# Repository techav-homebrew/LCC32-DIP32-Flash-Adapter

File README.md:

# LCC32-DIP32-Flash-Adapter
PCB for using LCC32 29F0x0 flash ROM chips in DIP32 sockets

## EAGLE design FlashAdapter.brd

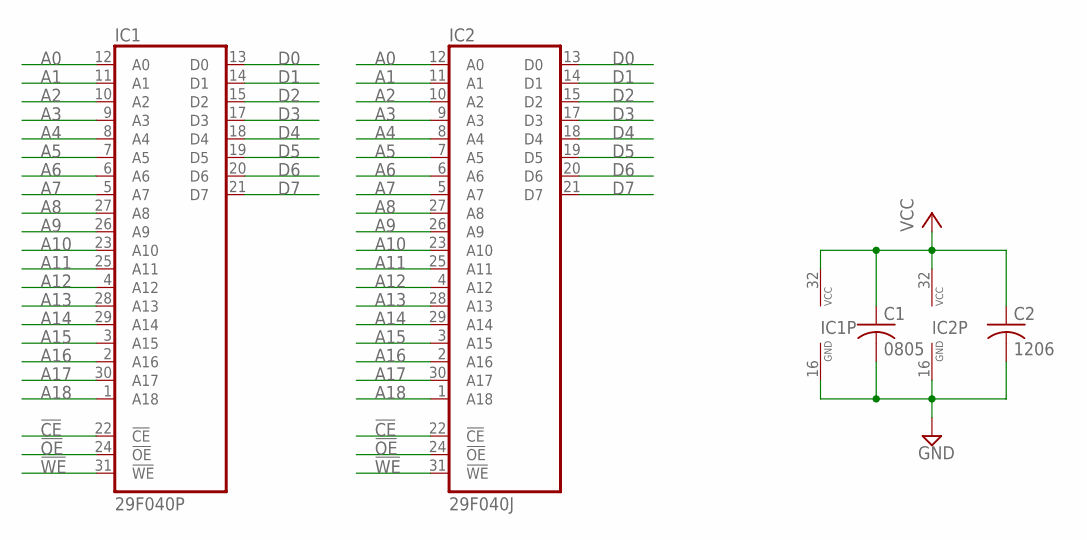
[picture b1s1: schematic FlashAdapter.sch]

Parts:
C1: 0805; C0805
C2: 1206; C1206
IC1: 29F040P; DIL32-3
IC2: 29F040J; S32

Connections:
!CE: IC1.22 (!CE), IC2.22 (!CE)
!OE: IC1.24 (!OE), IC2.24 (!OE)
!WE: IC1.31 (!WE), IC2.31 (!WE)
A0: IC1.12 (A0), IC2.12 (A0)
A1: IC1.11 (A1), IC2.11 (A1)
A2: IC1.10 (A2), IC2.10 (A2)
A3: IC1.9 (A3), IC2.9 (A3)
A4: IC1.8 (A4), IC2.8 (A4)
A5: IC1.7 (A5), IC2.7 (A5)
A6: IC1.6 (A6), IC2.6 (A6)
A7: IC1.5 (A7), IC2.5 (A7)
A8: IC1.27 (A8), IC2.27 (A8)
A9: IC1.26 (A9), IC2.26 (A9)
A10: IC1.23 (A10), IC2.23 (A10)
A11: IC1.25 (A11), IC2.25 (A11)
A12: IC1.4 (A12), IC2.4 (A12)
A13: IC1.28 (A13), IC2.28 (A13)
A14: IC1.29 (A14), IC2.29 (A14)
A15: IC1.3 (A15), IC2.3 (A15)
A16: IC1.2 (A16), IC2.2 (A16)
A17: IC1.30 (A17), IC2.30 (A17)
A18: IC1.1 (A18), IC2.1 (A18)
D0: IC1.13 (D0), IC2.13 (D0)
D1: IC1.14 (D1), IC2.14 (D1)
D2: IC1.15 (D2), IC2.15 (D2)
D3: IC1.17 (D3), IC2.17 (D3)
D4: IC1.18 (D4), IC2.18 (D4)
D5: IC1.19 (D5), IC2.19 (D5)
D6: IC1.20 (D6), IC2.20 (D6)
D7: IC1.21 (D7), IC2.21 (D7)
GND: C1.2, C2.2, IC1.16 (GND), IC2.16 (GND)
VCC: C1.1, C2.1, IC1.32 (VCC), IC2.32 (VCC)

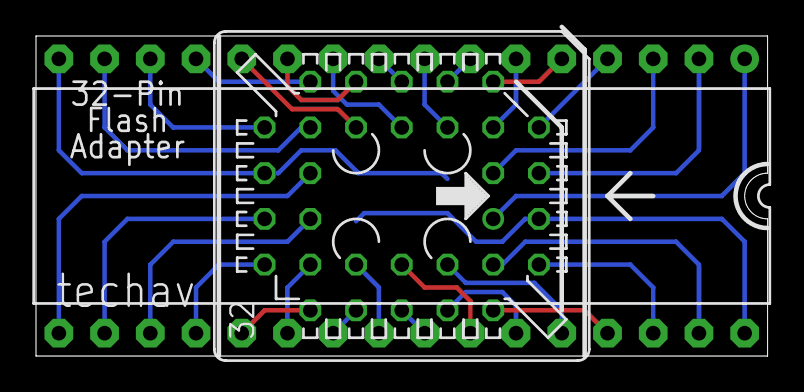
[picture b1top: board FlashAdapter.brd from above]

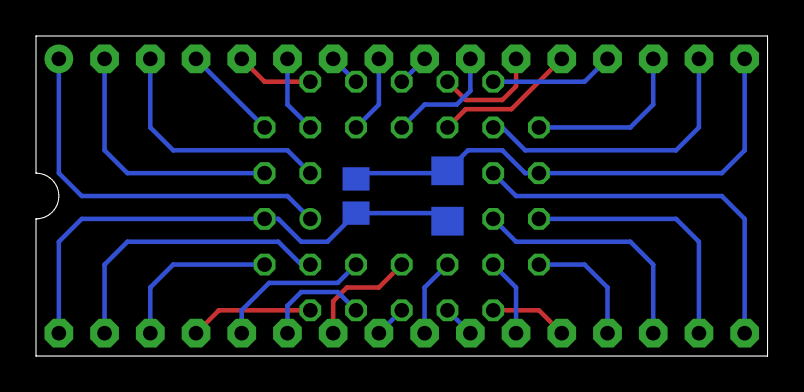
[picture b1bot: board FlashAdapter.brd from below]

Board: 2 copper layers, 40.6 x 17.8 mm, 4 parts (2 on the bottom side), 32 nets.

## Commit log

2023-01-17 Schematics & Gerbers
